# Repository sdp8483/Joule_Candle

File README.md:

# Joule Thief Candle
[Original Blog Post](https://samueldperry.com/2016/12/18/single-led-candle-joule-thief/)

## Repository Links
* [KiCAD Project File](Joule_Candle.pro)
* [Component Datasheets](datasheets/)
* [Schematic PDF](pdf/Joule_Candle.pdf)
* [PCB 3D Renders](images/)
* [PCB Gerber Output](gerber/)

## BOM
Below is the BOM for assembling a Joule Thief Candle. Similar 0603 resistors and 3mm LEDs can be substituted for the parts listed below if not available.

|Description                   |Reference|Value       |Manufacture             |Mfg Part Number|Supplier|Supplier Part Number                                                                                             |
|------------------------------|---------|------------|------------------------|---------------|--------|-----------------------------------------------------------------------------------------------------------------|
|BATTERY CONTACT AA SIZE       |BT1      |AA          |Memory Protected Devices|BK-92          |Digikey |[BK-92-ND](https://www.digikey.com/products/en?keywords=BK-92-ND)                                                |
|RES SMD 6.8K OHM 5% 1/10W 0603|R1       |6.8K        |Yageo                   |RC0603JR-076K8L|Digikey |[311-6.8KGRTR-ND](https://www.digikey.com/products/en?keywords=311-6.8KGRTR-ND)                                  |
|Warm White 3mm LED            |D1       |LED         |Chanzon                 |100F3T-PT-WH-WW|Amazon  |[B01BTYHOLS](https://www.amazon.com/Transparent-Lighting-Electronics-Components-Emitting/dp/B01BTYHOLS)          |
|TRANS NPN 45V 0.8A SOT-23     |Q1       |BC817-25    |Micro Commercial        |BC817-25-TP    |Digikey |[BC817-25-TPMSCT-ND](https://www.digikey.com/products/en?keywords=BC817-25-TPMSCT-ND)                            |
|CMC 51UH 200MA 2LN 2 KOHM SMD |L1       |SRF4532-510Y|Bourns                  |SRF4532-510Y   |Digikey |[SRF4532-510YCT-ND](https://www.digikey.com/product-detail/en/bourns-inc/SRF4532-510Y/SRF4532-510YCT-ND/3679940) |
|SWITCH SLIDE SPDT 100MA 12V   |S1       |SPDT        |C&K                     |OS102011MA1QN1 |Digikey |[CKN9559-ND](https://www.digikey.com/products/en?keywords=CKN9559-ND)                                            |

## Consumables
Below is a list of consumable items used during assembly and cleaning. Note that the exact consumable is not necessary, similar items can be substituted as needed.

|Description            |Mfg Part Number |Manufacture |Supplier |Supplier Part Number                                                                                                                                                       |
|-----------------------|----------------|------------|---------|---------------------------------------------------------------------------------------------------------------------------------------------------------------------------|
|Lead Free Solder Paste |SMD291SNL50T3   |Chip Quik   |Digikey  |[SMD291SNL50T3-ND](https://www.digikey.com/products/en?keywords=SMD291SNL50T3-ND)                                                                                          |
|Lead Free Solder Wire  |4944-112G       |MG Chemicals|Digikey  |[473-1251-ND](https://www.digikey.com/products/en?keywords=473-1251-ND)                                                                                                    |
|Rosin Flux             |835-100ML       |MG Chemicals|Amazon   |[B005DNR01Q](https://www.amazon.com/MG-Chemicals-Corrosive-Conductive-residue/dp/B005DNR01Q/ref=sr_1_1?s=industrial&ie=UTF8&qid=1509815006&sr=1-1&keywords=835-100ML&th=1) |
|Flux Cleaner           |4140-P          |MG Chemicals|Amazon   |[B005T8KKJY](https://www.amazon.com/MG-Chemicals-Remover-Boards-Liquid/dp/B005T8KKJY/ref=cm_cr_arp_d_product_top?ie=UTF8)                                                  |
|Paper Wipes 			|TP				 |			  |			|                                                                                                                                                                           |

## Tools
Below is a list of tooling used during assembly with part number of the tools I used, note that the exact tool is not needed and similar tools can be substituted as needed.
* Temperature Controlled Soldering Iron: Hakko FX-888D with T18-D16 tip
* SMD Hot Air Re-flow Station: X-Tronic 4000 Series
* Flush Cut Wire Cutters (side cutters?)
* Anti Static Brush
* Xacto Knife
* Fine Tip Tweezers
* Syringe: Monoject 412

## 3D Printed Assembly Tooling
Below is a list of 3D printed tooling that is useful during assembly. This tooling is not necessary for small assembly batches but becomes very useful if assembling 10 or more units at a time. 
3D model files and STL files for printing are linked down below.

|Description|Fusion 360 3D File|STL File|
|-----------|-------|--------|
|[Switch Solder Jig](assembly/3d_printed_tooling/images/switch_solder_jig.png)|[f3d](assembly/3d_printed_tooling/fusion_360/switch_solder_jig.f3d)|[stl](assembly/3d_printed_tooling/stl/switch_solder_jig.stl)|
|[LED Lead Cutting Guide](assembly/3d_printed_tooling/images/led_lead_cutting_guide.png)|[f3d](assembly/3d_printed_tooling/fusion_360/led_lead_cutting_guide.f3d)|[stl](assembly/3d_printed_tooling/stl/led_lead_cutting_guide.stl)|
|[LED Solder Jig](assembly/3d_printed_tooling/images/led_solder_jig.png)|[f3d](assembly/3d_printed_tooling/fusion_360/led_solder_jig.f3d)|[stl](assembly/3d_printed_tooling/stl/led_solder_jig.stl)|
|[Modified Vise Jaws\*](assembly/3d_printed_tooling/images/modified_vise_jaws.png)|[f3d](assembly/3d_printed_tooling/fusion_360/vise_jaws.f3d)|[stl](assembly/3d_printed_tooling/stl/modified_sliding_jaw_plate.stl), [stl](assembly/3d_printed_tooling/stl/modified_base_jaw_plate.stl)|

\*The modified vise jaws fit the [Yet ANOTHER Machine Vise](https://www.thingiverse.com/thing:2064269) by TheGoofy

## Assembly Instructions
1. Using the Xacto knife or other fine tipped instrument apply a small amount of solder paste to the pads for the NPN transistor and the 6.8K resistor. Less solder paste is better. **Buy a stencil next time!**
2. With a pair of tweezers place the transistor and resistor on the pads.
3. Turn on the re-flow solder station hot air gun with moderate to high air flow.
	* For lead free solder a hot air temperature of about 410C is good for all SMD parts.
	* For lead solder a hot air temperature of about 380C is good for all SMD parts.
4. Apply heat evenly around the transistor and resistor until the solder is shiny and flows. Pin 2 of the NPN transistor seems to be the last pad to flow.
5. Allow the PCB to cool before applying solder paste to the pads for the SRF4532 common mode choke. Again less is better and **buy a stencil next time!**
6. Using a pair of tweezers place the common mode choke on the pads.
7. Apply heat evenly around the common mode choke until the solder paste is shiny and flows.
8. Turn on the soldering iron.
	* For lead free solder a soldering iron temperature of about 415C is good for all through hole parts.
	* For lead solder a soldering iron temperature of about 365C is good for all through hole parts.
9. Using the switch soldering jig solder the slide switch in place. Start with the middle pin and work out. Additional flux is not necessary if you are using rosin core solder.
10. Using the LED lead cutting guide cut the leads of an inserted 3mm LED flush to the guide using flush cut wire cutters.
11. Using the LED soldering jig place the PCB into the jig then place the LED into the jig near the solder pads for the LED. Notice that the orientation indicator of the LED requires that the LED only fits in one orientation on the jig. Solder the LED to the PCB.
12. Place the battery clips into the PCB, the clips will stay in place.
13. Place the PCB into the modified vise jaws. Apply a few drops of rosin flux to the battery terminal solder pins and pads.
14. Solder the battery clips into place. The battery clips will act like heat sinks and require the soldering iron tip to be applied a few seconds longer then normal before applying solder.
15. Allow the PCB to cool completely.
16. Place the assembled PCB into a small amount of the flux cleaner and let is soak for a minute or two.
17. Remove from the flux cleaner and use the anti static brush to remove any left over flux.
18. Place the assembled PCB into a fresh amount of the flux cleaner for only a few seconds.
19. After removing from the flux cleaner use some paper wipes (toilet paper) to soak up the flux cleaner from the PCB to remove any left over residue. Repeat this step if necessary to remove stubborn residue.
20. Allow the flux cleaner to completely evaporate before testing with a AA battery.

## Other
If you do not want to bother with ordering components and assembly I do sell these on Tindie.

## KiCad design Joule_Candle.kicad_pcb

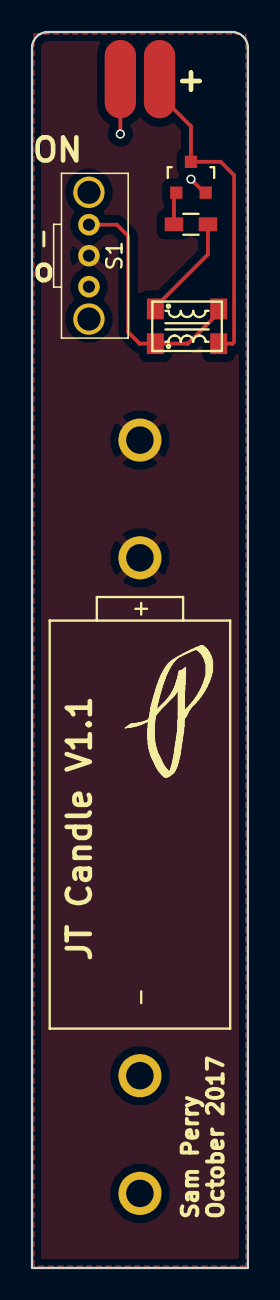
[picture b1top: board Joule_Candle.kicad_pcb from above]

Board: 2 copper layers, 14.0 x 80.0 mm, 7 parts (0 on the bottom side), 6 nets.

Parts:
BT1: AA; AA_PCB-Clip
D1: LED; 3mm_PCB_Edge
L1: SRF4532-510Y
LOGO: P-Logo_Small
Q1: BC817-40; SOT-23
R1: 1K; R_0603_HandSoldering
S1: SPDT; SPDT_OS102011MA1QN1

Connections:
GND: BT1.2, D1.1, Q1.2
unnamed: BT1.1, S1.2
unnamed: D1.2, L1.2, Q1.3
unnamed: L1.1, L1.3, S1.1
unnamed: L1.4, R1.1
unnamed: Q1.1, R1.2

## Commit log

2017-10-01 add blog url
2017-10-22 change value of R1
2017-10-22 change LED footprint
2017-10-22 remove 3d shapes
2017-10-22 update silkscreen
2017-10-22 generate gerber
2017-10-22 update silkscreen version
2017-10-22 update gerber output
2017-10-22 ignore xlsx files now
2017-10-23 update lib to cache lib
2017-10-23 update schematic with part info. Add datasheets to dir
2017-10-30 remove dummy
2017-10-31 move name/date text to F.SilkS from F.Mask to prevent battery clip shorting to Vcc, dummy move
2017-11-01 Add BOM
2017-11-01 Remove datasheet from BOM table
2017-11-01 Update with more BOM and tool info
2017-11-04 updated with 3d printed assembly tooling
2017-11-04 3d printed assembly tooling
2017-11-04 update with supplier links
2017-11-04 assembly instructions
2017-11-04 fix blog post link
2017-11-04 fix led link
2017-11-04 fix sub lists
2017-11-05 shameless tindie plug
2017-11-05 fix link
2017-11-05 update rev
2017-11-05 output scema to pdf
2017-11-05 update scehma
2017-11-05 not needed
2017-11-05 3D PCB images
2017-11-05 add repository links
2017-11-05 repository links header renamed
2017-11-05 unordered list for repo links, formatting issue correction
2017-12-10 assembled pcb pics
2017-12-10 add sw DPDT x2
2017-12-10 add footprint for smd switch
2017-12-10 start smd switch but $$$, not changing.
2017-12-10 add footprint for smd battery clips
2017-12-10 add new componet datasheets
2017-12-10 change dpdt connections for porper switch operation at orientation
2017-12-10 modify silkscreen
2017-12-10 update pcb with smd components
2017-12-10 update gerber with new pcb
2017-12-10 ignore zipped gerber
2017-12-10 new gerber zip
2017-12-10 fixed zip ignore
2017-12-10 save proj
2018-01-08 update gerber
2018-01-08 update gerber, add f.paste for stencil
2018-01-08 save after plot gerber f.paste
